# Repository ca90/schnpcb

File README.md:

schnpcb
=======

Schematics and PCB files of my Projects

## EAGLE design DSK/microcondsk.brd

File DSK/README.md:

DSK
=======================

The SCH and PCB layouts for the DSK or ISP using 8051 microcontroller.
-Darshil Chanpura

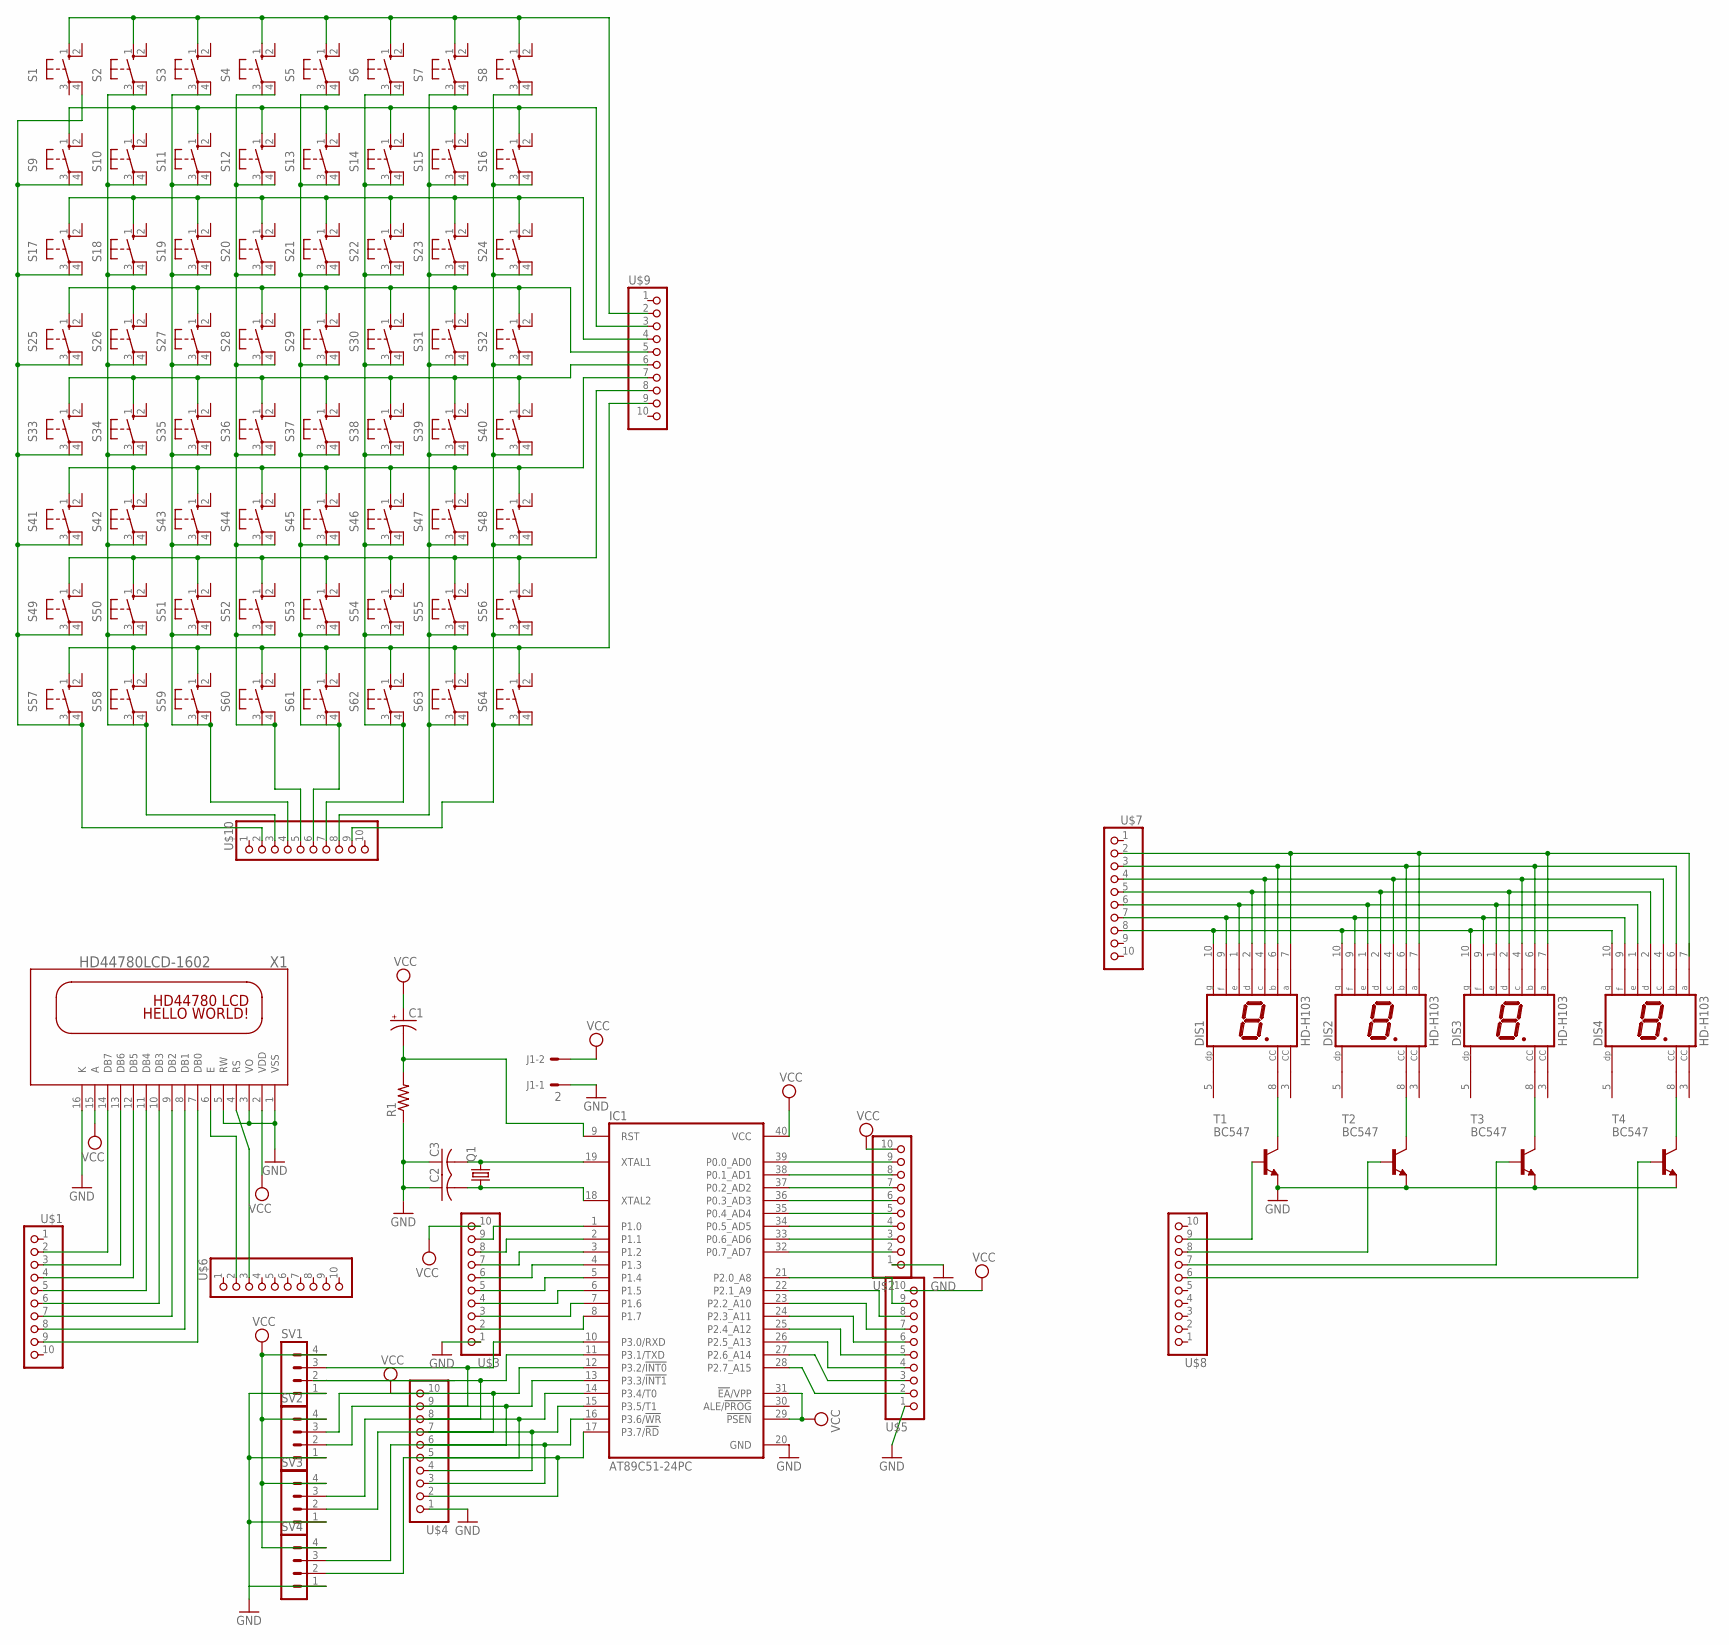
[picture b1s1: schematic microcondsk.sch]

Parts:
C1: CPOL-USE2-5; E2-5
C2, C3: C-US025-025X050; C025-025X050
DIS1, DIS2, DIS3, DIS4: HD-H103; HDSP-M
IC1: AT89C51-24PC; DIL40
J1: 2; 6410-02
Q1: CRYSTALHC49U-V; HC49U-V
R1: R-US_0204/7; 0204/7
S1, S2, S3, S4, S5, S6, S7, S8, S9, S10, S11, S12, S13, S14, S15, S16, S17, S18, S19, S20, S21, S22, S23, S24, S25, S26, S27, S28, S29, S30, S31, S32, S33, S34, S35, S36, S37, S38, S39, S40, S41, S42, S43, S44, S45, S46, S47, S48, S49, S50, S51, S52, S53, S54, S55, S56, S57, S58, S59, S60, S61, S62, S63, S64: 10-XX; B3F-10XX
SV1, SV2, SV3, SV4: MA04-1
T1, T2, T3, T4: BC547; TO92
U$1, U$2, U$3, U$4, U$5, U$6, U$7, U$8, U$9, U$10: PINHD-1X10; 1X10-BIG
X1: HD44780LCD-1602; LCD1602

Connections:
GND: C2.1, C3.1, IC1.20 (GND), J1.1, R1.1, SV1.1, SV2.1, SV3.1, SV4.1, T1.1 (E), T2.1 (E), T3.1 (E), T4.1 (E), U$2.1, U$3.1, U$4.1, U$5.1, X1.1 (VSS), X1.3 (VO), X1.5 (RW), X1.16 (K)
unnamed: IC1.8 (P1.7), U$3.2
unnamed: C1.-, IC1.9 (RST), R1.2
unnamed: IC1.7 (P1.6), U$3.3
unnamed: C3.2, IC1.19 (XTAL1), Q1.2
unnamed: C2.2, IC1.18 (XTAL2), Q1.1
unnamed: IC1.6 (P1.5), U$3.4
unnamed: IC1.5 (P1.4), U$3.5
unnamed: IC1.4 (P1.3), U$3.6
unnamed: IC1.3 (P1.2), U$3.7
unnamed: IC1.2 (P1.1), U$3.8
unnamed: IC1.1 (P1.0), U$3.9
unnamed: IC1.10 (P3.0/RXD), SV1.3, U$4.9
unnamed: IC1.11 (P3.1/TXD), SV1.2, U$4.8
unnamed: IC1.12 (P3.2/!INT0), SV2.3, U$4.7
unnamed: IC1.13 (P3.3/!INT1), SV2.2, U$4.6
unnamed: DIS1.8 (CC), T1.3 (C)
unnamed: IC1.15 (P3.5/T1), SV3.2, U$4.4
unnamed: IC1.16 (P3.6/!WR), SV4.3, U$4.3
unnamed: IC1.17 (P3.7/!RD), SV4.2, U$4.2
unnamed: IC1.32 (P0.7_AD7), U$2.2
unnamed: IC1.33 (P0.6_AD6), U$2.3
unnamed: IC1.34 (P0.5_AD5), U$2.4
unnamed: IC1.35 (P0.4_AD4), U$2.5
unnamed: IC1.36 (P0.3_AD3), U$2.6
unnamed: IC1.37 (P0.2_AD2), U$2.7
unnamed: IC1.38 (P0.1_AD1), U$2.8
unnamed: IC1.39 (P0.0_AD0), U$2.9
unnamed: IC1.21 (P2.0_A8), U$5.9
unnamed: IC1.22 (P2.1_A9), U$5.8
unnamed: IC1.23 (P2.2_A10), U$5.7
unnamed: IC1.24 (P2.3_A11), U$5.6
unnamed: IC1.25 (P2.4_A12), U$5.5
unnamed: IC1.26 (P2.5_A13), U$5.4
unnamed: IC1.28 (P2.7_A15), U$5.2
unnamed: IC1.27 (P2.6_A14), U$5.3
unnamed: U$1.2, X1.14 (DB7)
unnamed: U$1.3, X1.13 (DB6)
unnamed: U$1.4, X1.12 (DB5)
unnamed: U$1.5, X1.11 (DB4)
unnamed: U$1.6, X1.10 (DB3)
unnamed: U$1.7, X1.9 (DB2)
unnamed: U$1.8, X1.8 (DB1)
unnamed: U$1.9, X1.7 (DB0)
unnamed: U$6.2, X1.6 (E)
unnamed: U$6.3, X1.4 (RS)
unnamed: DIS2.8 (CC), T2.3 (C)
unnamed: IC1.14 (P3.4/T0), SV3.3, U$4.5
unnamed: DIS3.8 (CC), T3.3 (C)
unnamed: DIS4.8 (CC), T4.3 (C)
unnamed: T1.2 (B), U$8.9
unnamed: S1.1 (S), S2.1 (S), S3.1 (S), S4.1 (S), S5.1 (S), S6.1 (S), S7.1 (S), S8.1 (S), U$9.2
unnamed: T4.2 (B), U$8.6
unnamed: T3.2 (B), U$8.7
unnamed: DIS1.10 (G), DIS2.10 (G), DIS3.10 (G), DIS4.10 (G), U$7.8
unnamed: DIS1.9 (F), DIS2.9 (F), DIS3.9 (F), DIS4.9 (F), U$7.7
unnamed: DIS1.1 (E), DIS2.1 (E), DIS3.1 (E), DIS4.1 (E), U$7.6
unnamed: DIS1.2 (D), DIS2.2 (D), DIS3.2 (D), DIS4.2 (D), U$7.5
unnamed: DIS1.4 (C), DIS2.4 (C), DIS3.4 (C), DIS4.4 (C), U$7.4
unnamed: DIS1.6 (B), DIS2.6 (B), DIS3.6 (B), DIS4.6 (B), U$7.3
unnamed: DIS1.7 (A), DIS2.7 (A), DIS3.7 (A), U$7.2
unnamed: T2.2 (B), U$8.8
unnamed: S9.1 (S), S10.1 (S), S11.1 (S), S12.1 (S), S13.1 (S), S14.1 (S), S15.1 (S), S16.1 (S), U$9.3
unnamed: S1.4 (P1), S9.4 (P1), S17.4 (P1), S25.4 (P1), S33.4 (P1), S41.4 (P1), S49.4 (P1), S57.4 (P1), U$10.2
unnamed: S2.4 (P1), S10.4 (P1), S18.4 (P1), S26.4 (P1), S34.4 (P1), S42.4 (P1), S50.4 (P1), S58.4 (P1), U$10.3
unnamed: S3.4 (P1), S11.4 (P1), S19.4 (P1), S27.4 (P1), S35.4 (P1), S43.4 (P1), S51.4 (P1), S59.4 (P1), U$10.4
unnamed: S4.4 (P1), S12.4 (P1), S20.4 (P1), S28.4 (P1), S36.4 (P1), S44.4 (P1), S52.4 (P1), S60.4 (P1), U$10.5
unnamed: S5.4 (P1), S13.4 (P1), S21.4 (P1), S29.4 (P1), S37.4 (P1), S45.4 (P1), S53.4 (P1), S61.4 (P1), U$10.6
unnamed: S6.4 (P1), S14.4 (P1), S22.4 (P1), S30.4 (P1), S38.4 (P1), S46.4 (P1), S54.4 (P1), S62.4 (P1), U$10.7
unnamed: S7.4 (P1), S15.4 (P1), S23.4 (P1), S31.4 (P1), S39.4 (P1), S47.4 (P1), S55.4 (P1), S63.4 (P1), U$10.8
unnamed: S8.4 (P1), S16.4 (P1), S24.4 (P1), S32.4 (P1), S40.4 (P1), S48.4 (P1), S56.4 (P1), S64.4 (P1), U$10.9
unnamed: S17.1 (S), S18.1 (S), S19.1 (S), S20.1 (S), S21.1 (S), S22.1 (S), S23.1 (S), S24.1 (S), U$9.4
unnamed: S25.1 (S), S26.1 (S), S27.1 (S), S28.1 (S), S29.1 (S), S30.1 (S), S31.1 (S), S32.1 (S), U$9.5
unnamed: S33.1 (S), S34.1 (S), S35.1 (S), S36.1 (S), S37.1 (S), S38.1 (S), S39.1 (S), S40.1 (S), U$9.6
unnamed: S41.1 (S), S42.1 (S), S43.1 (S), S44.1 (S), S45.1 (S), S46.1 (S), S47.1 (S), S48.1 (S), U$9.7
unnamed: S49.1 (S), S50.1 (S), S51.1 (S), S52.1 (S), S53.1 (S), S54.1 (S), S55.1 (S), S56.1 (S), U$9.8
unnamed: S57.1 (S), S58.1 (S), S59.1 (S), S60.1 (S), S61.1 (S), S62.1 (S), S63.1 (S), S64.1 (S), U$9.9
VCC: C1.+, IC1.29 (!PSEN), IC1.31 (!EA!/VPP), IC1.40 (VCC), J1.2, SV1.4, SV2.4, SV3.4, SV4.4, U$2.10, U$3.10, U$4.10, U$5.10, X1.2 (VDD), X1.15 (A)

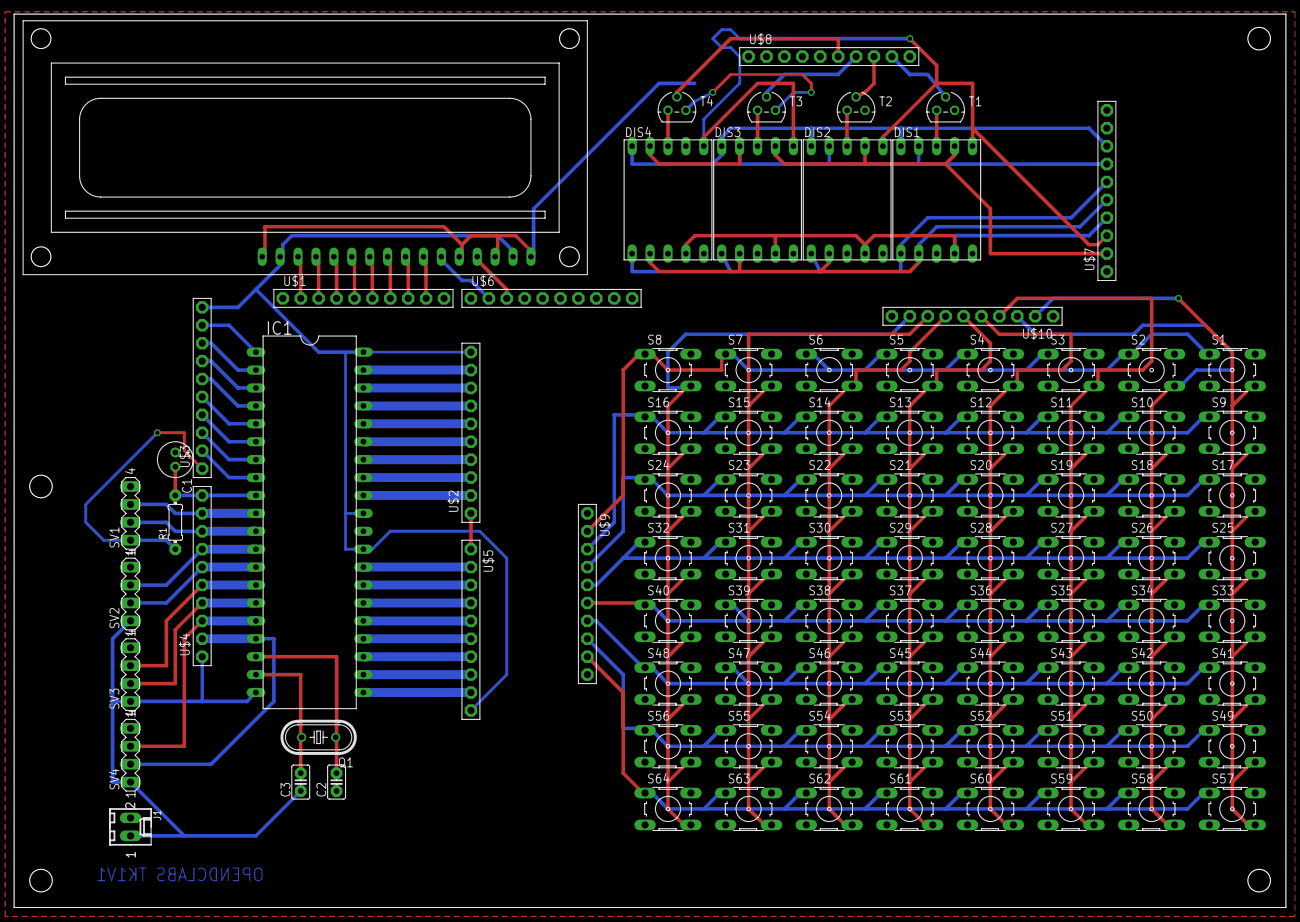
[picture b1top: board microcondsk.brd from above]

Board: 2 copper layers, 180.3 x 126.7 mm, 94 parts (0 on the bottom side), 78 nets.

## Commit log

2012-12-30 8051 Microcontroller DSK or ISP
    LCD, 8x8 Matrix Keyboard, 4 Seven-Segments, Headers for all pins
2012-12-30 README.md Added
